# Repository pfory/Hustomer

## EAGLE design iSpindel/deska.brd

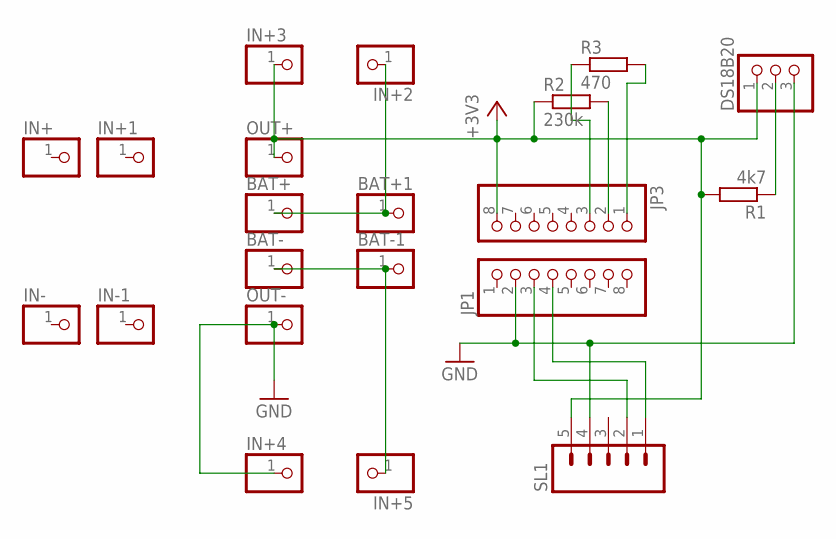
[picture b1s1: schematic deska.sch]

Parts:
BAT+, BAT+1: PINHD-1X1; 1X01
BAT-, BAT-1: PINHD-1X1; 1X01
DS18B20: PINHD-1X3; 1X03
IN+, IN+1, IN+2, IN+3, IN+4, IN+5: PINHD-1X1; 1X01
IN-, IN-1: PINHD-1X1; 1X01
JP1, JP3: PINHD-1X8; 1X08
OUT+: PINHD-1X1; 1X01
OUT-: PINHD-1X1; 1X01
R1: 4k7; 0204/7
R2: 230k; 0204/7
R3: 470; 0204/7
SL1: M05; 05P

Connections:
+3V3: DS18B20.1, IN+3.1, JP3.8, OUT+.1, R1.2, R2.1, SL1.5
GND: DS18B20.3, IN+4.1, JP1.2, OUT-.1, SL1.4
unnamed: JP3.2, R2.2
unnamed: DS18B20.2, R1.1
unnamed: JP3.1, R3.2
unnamed: JP3.3, R3.1
unnamed: BAT+.1, BAT+1.1, IN+2.1
unnamed: BAT-.1, BAT-1.1, IN+5.1
unnamed: JP1.3, SL1.2
unnamed: JP1.4, SL1.1

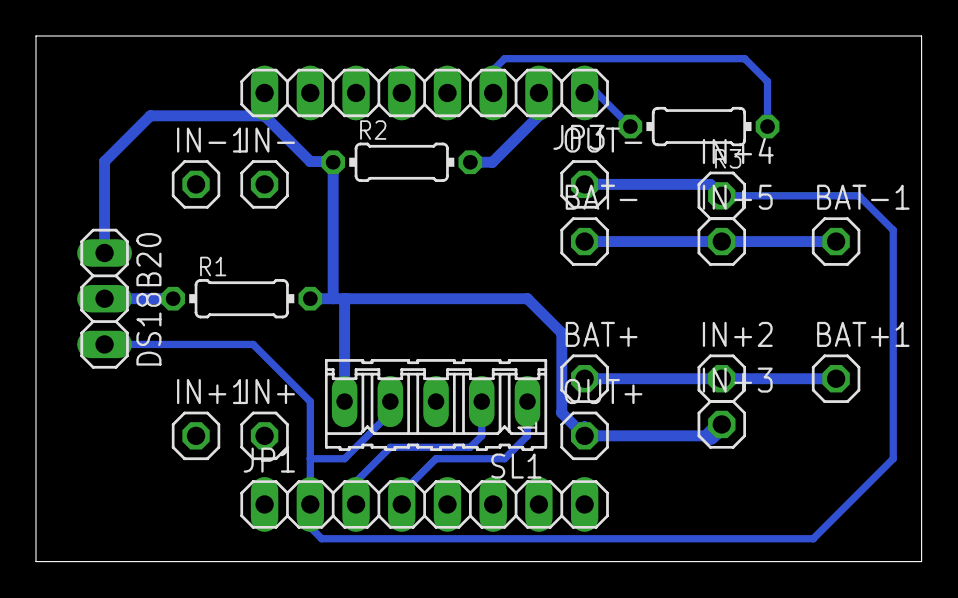
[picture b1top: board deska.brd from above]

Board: 2 copper layers, 49.2 x 29.2 mm, 21 parts (0 on the bottom side), 10 nets.

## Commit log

2018-01-11 init
2018-01-13 zmeny desky
2018-01-28 deska
2018-01-31 upravy desky
2018-02-11 kalib
2018-10-03 uprava desky
